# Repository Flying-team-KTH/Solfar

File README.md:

# Solfar
Repository for the solfar aircraft

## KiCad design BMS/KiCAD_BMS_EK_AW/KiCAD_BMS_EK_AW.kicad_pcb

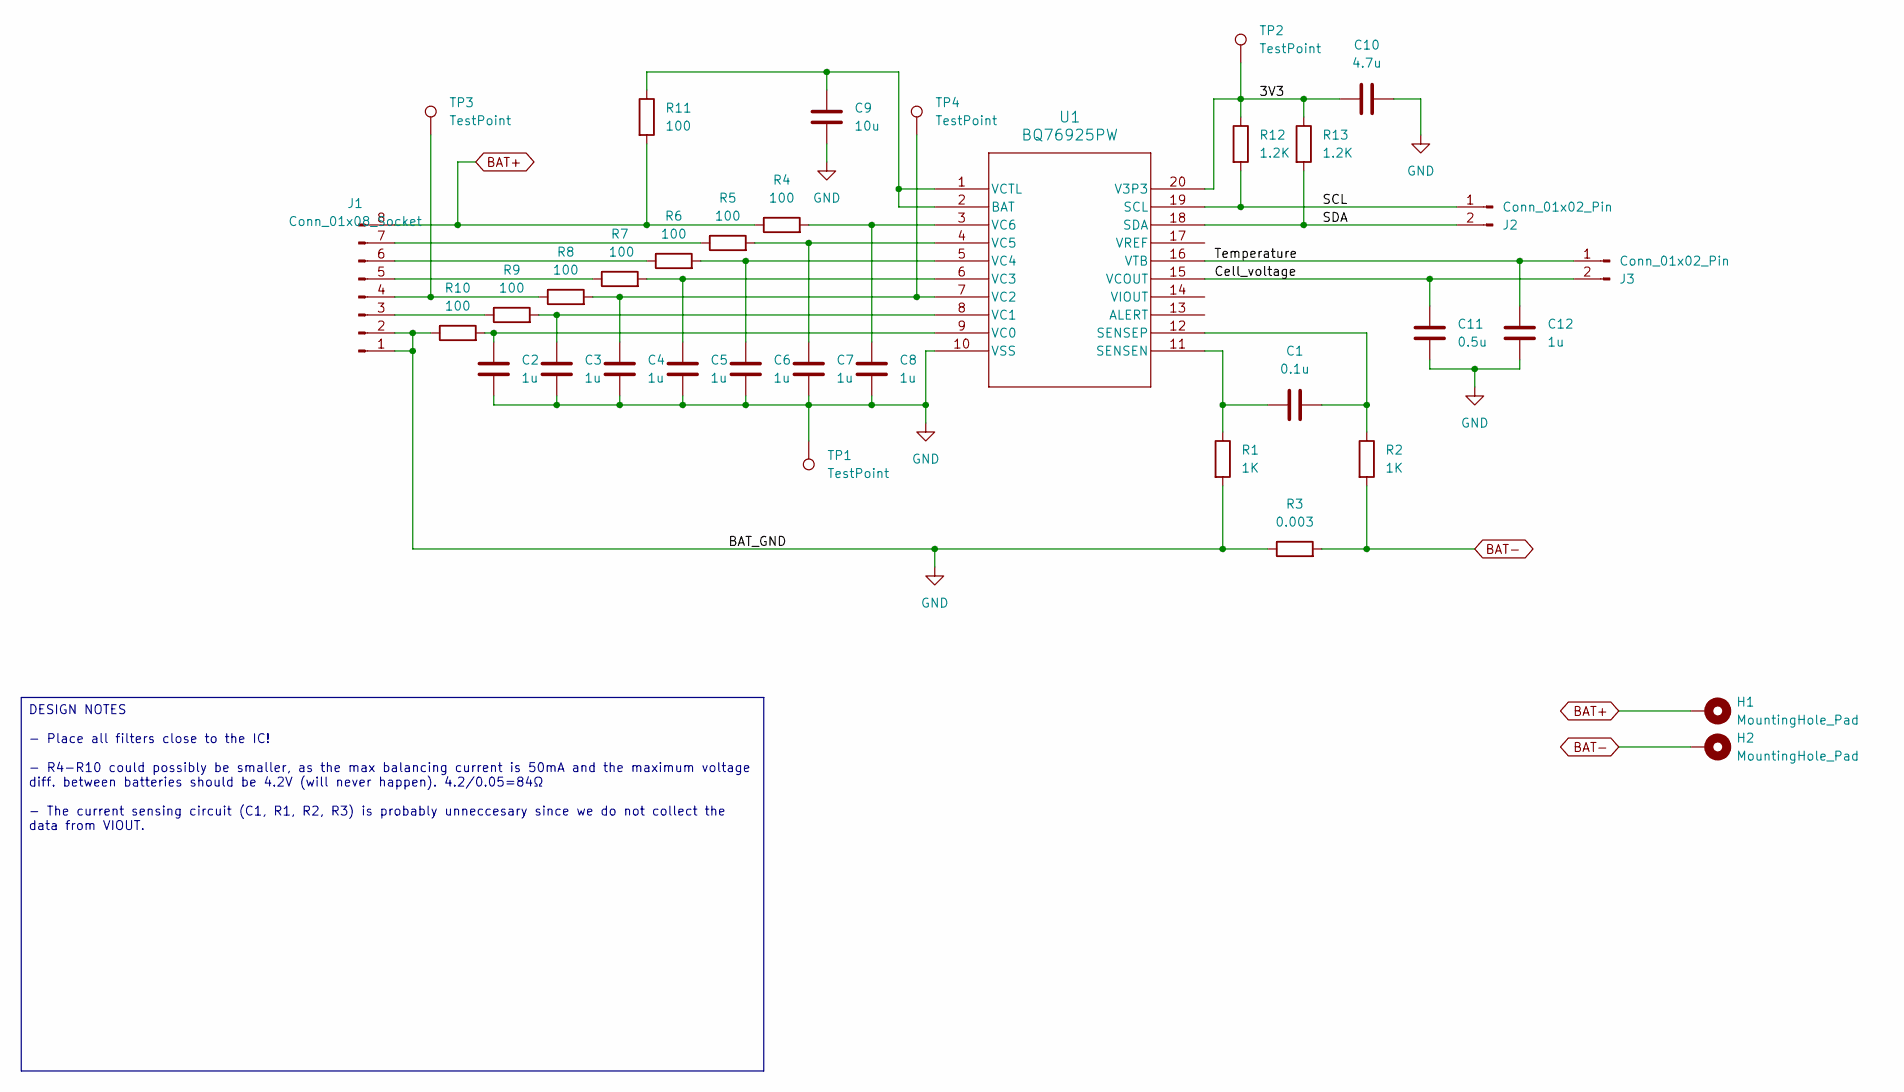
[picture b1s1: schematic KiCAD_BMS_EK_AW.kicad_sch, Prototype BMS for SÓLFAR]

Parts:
C1: 0.1u; C_1210_3225Metric_Pad1.33x2.70mm_HandSolder
C2, C3, C4, C5, C6, C7, C8, C12: 1u; C_1210_3225Metric_Pad1.33x2.70mm_HandSolder
C9: 10u; C_1210_3225Metric_Pad1.33x2.70mm_HandSolder
C10: 4.7u; C_1210_3225Metric_Pad1.33x2.70mm_HandSolder
C11: 0.5u; C_1210_3225Metric_Pad1.33x2.70mm_HandSolder
H1, H2: MountingHole_Pad; MountingHole_2.2mm_M2_DIN965_Pad
J1: Conn_01x08_Socket; JST_GH_BM08B-GHS-TBT_1x08-1MP_P1.25mm_Vertical
J2, J3: Conn_01x02_Pin; JST_GH_BM02B-GHS-TBT_1x02-1MP_P1.25mm_Vertical
R1, R2: 1K; R_1206_3216Metric_Pad1.30x1.75mm_HandSolder
R3: 0.003; R_2512_6332Metric_Pad1.40x3.35mm_HandSolder
R4, R5, R6, R7, R8, R9, R10, R11: 100; R_1206_3216Metric_Pad1.30x1.75mm_HandSolder
R12, R13: 1.2K; R_1206_3216Metric_Pad1.30x1.75mm_HandSolder
TP1, TP2, TP3, TP4: TestPoint; TestPoint_THTPad_D1.5mm_Drill0.7mm
U1: BQ76925PW; TSSOP-20_4.4x6.5mm_P0.65mm

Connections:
/3V3: C10.1, R12.1, R13.1, TP2.1, U1.20 (V3P3)
/Cell_voltage: C11.1, J3.2, U1.15 (VCOUT)
/SCL: J2.1, R12.2, U1.19 (SCL)
/SDA: J2.2, R13.2, U1.18 (SDA)
/Temperature: C12.1, J3.1, U1.16 (VTB)
BAT+: H1.1, J1.8, R4.1, R11.2
BAT-: H2.1, R2.2, R3.2
GND: C2.2, C3.2, C4.2, C5.2, C6.2, C7.2, C8.2, C9.2, C10.2, C11.2, C12.2, J1.1, J1.2, R1.2, R3.1, R10.1, TP1.1, U1.10 (VSS)
unnamed: J1.3, R9.1
unnamed: J1.4, R8.1, TP3.1
unnamed: J1.5, R7.1
unnamed: J1.6, R6.1
unnamed: J1.7, R5.1
unnamed: C9.1, R11.1, U1.1 (VCTL), U1.2 (BAT)
unnamed: C1.1, R1.1, U1.11 (SENSEN)
unnamed: C1.2, R2.1, U1.12 (SENSEP)
unnamed: C2.1, R10.2, U1.9 (VC0)
unnamed: C3.1, R9.2, U1.8 (VC1)
unnamed: C4.1, R8.2, TP4.1, U1.7 (VC2)
unnamed: C5.1, R7.2, U1.6 (VC3)
unnamed: C6.1, R6.2, U1.5 (VC4)
unnamed: C7.1, R5.2, U1.4 (VC5)
unnamed: C8.1, R4.2, U1.3 (VC6)

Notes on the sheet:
DESIGN NOTES - Place all filters close to the IC! - R4-R10 could possibly be smaller, as the max balancing current is 50mA and the maximum voltage diff. between batteries should be 4.2V (will never happen). 4.2/0.05=84Ω - The current sensing circuit (C1, R1, R2, R3) is probably unneccesary since we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

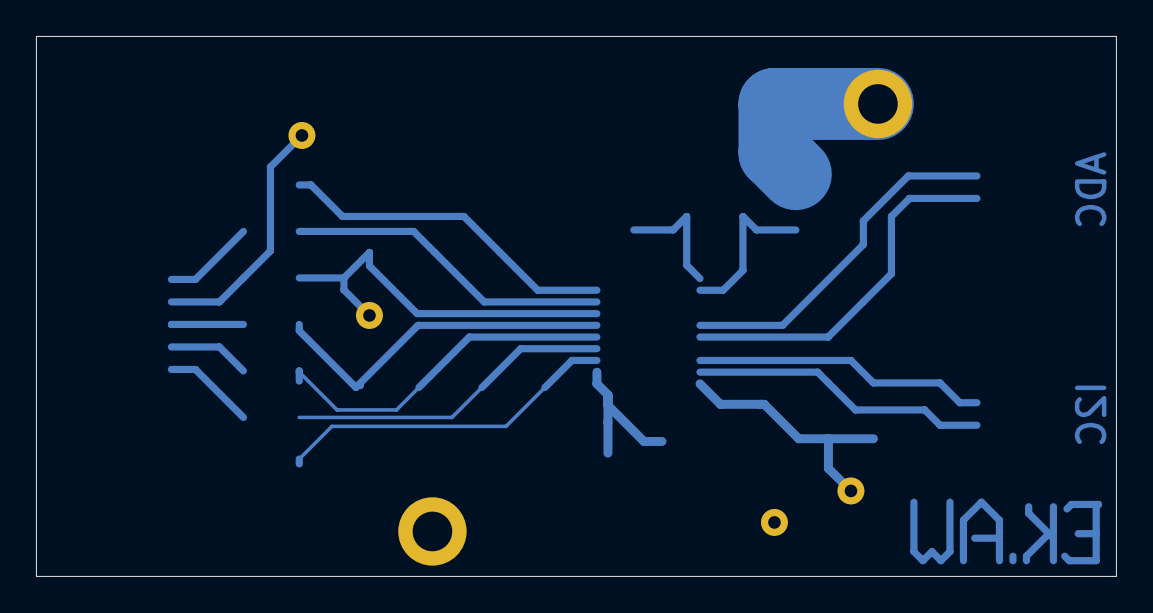
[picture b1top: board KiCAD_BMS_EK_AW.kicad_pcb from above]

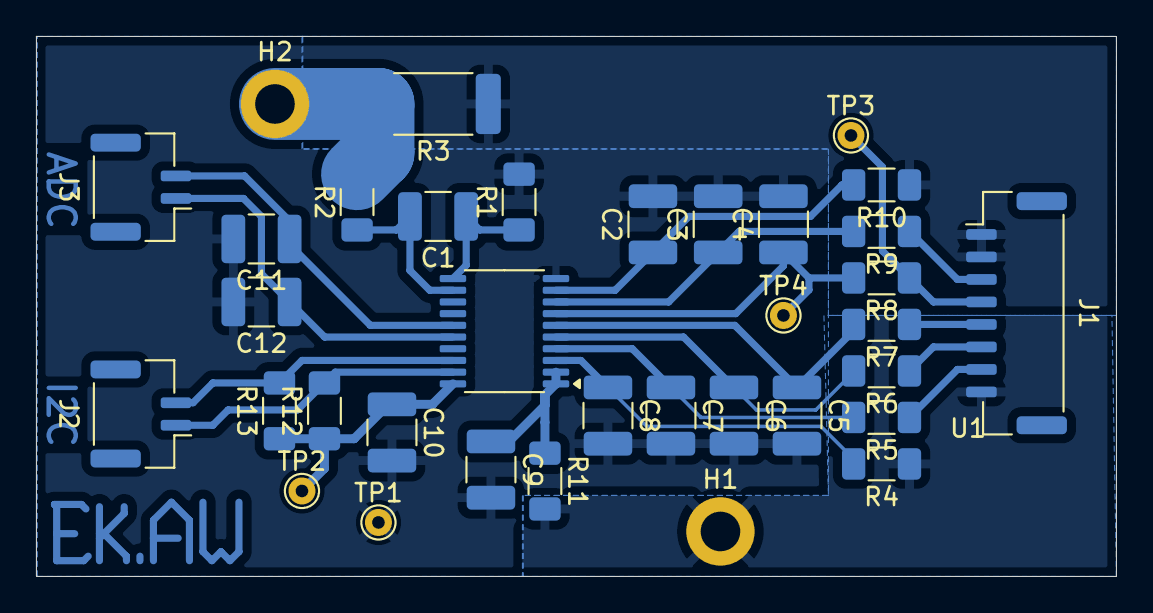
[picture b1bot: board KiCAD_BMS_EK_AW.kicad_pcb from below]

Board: 2 copper layers, 60.0 x 30.0 mm, 35 parts (35 on the bottom side), 23 nets.

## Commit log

2026-01-28 Added code and report for solfar BMS system
2026-01-28 Added ignore for general system files and KiCad
2026-01-28 KiCad project as described in AW,EK report
2026-01-28 Initial plan
2026-01-28 Remove all .DS_Store files from repository
